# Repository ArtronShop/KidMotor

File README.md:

# KidMotor

บอร์ดขับมอเตอร์สำหรับใช้งานกับ KidBright32 - https://www.ioxhop.com/

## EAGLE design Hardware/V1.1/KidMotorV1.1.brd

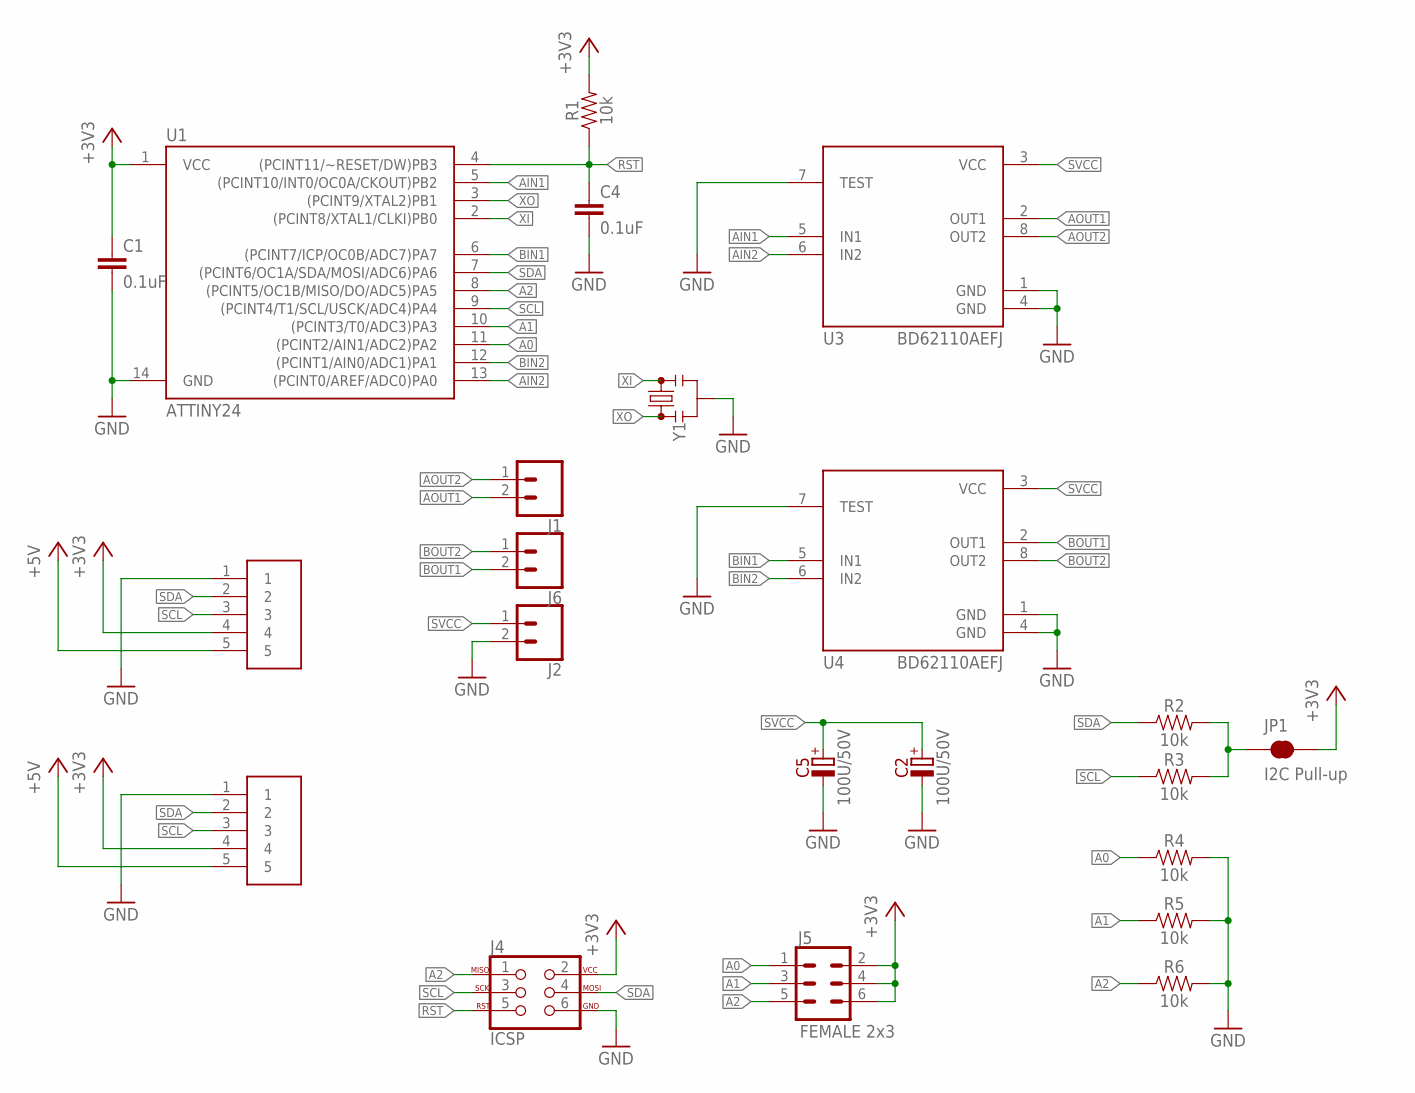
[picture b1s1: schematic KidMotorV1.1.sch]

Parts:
C1, C4: 0.1uF; 0603
C2, C5: 100U/50V; E3,5-8
J1, J2, J6: CONN_025MM; SCREWTERMINAL-5MM-2
J4: ICSP; 2X3
J5: FEMALE 2x3; 2X3
JP1: I2C Pull-up; SMT-JUMPER_2_NC_TRACE_SILK
R1, R2, R3, R4, R5, R6: 10k; 0603
U1: ATTINY24; SO14
U3, U4: BD62110AEFJ; HTSOP-J8
U$2, U$5: JST5PIN
Y1: RESONATORSMD-3.2X1.3; RESONATOR-SMD-3.2X1.3

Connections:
+3V3: C1.1, J4.2, J5.2, J5.4, J5.6, JP1.2, R1.2, U1.1 (VCC), U$2.4, U$5.4
+5V: U$2.5, U$5.5
A0: J5.1, R4.1, U1.11 ((PCINT2/AIN1/ADC2)PA2)
A1: J5.3, R5.1, U1.10 ((PCINT3/T0/ADC3)PA3)
A2: J4.1, J5.5, R6.1, U1.8 ((PCINT5/OC1B/MISO/DO/ADC5)PA5)
AIN1: U1.5 ((PCINT10/INT0/OC0A/CKOUT)PB2), U3.5 (IN1)
AIN2: U1.13 ((PCINT0/AREF/ADC0)PA0), U3.6 (IN2)
AOUT1: J1.2, U3.2 (OUT1)
AOUT2: J1.1, U3.8 (OUT2)
BIN1: U1.6 ((PCINT7/ICP/OC0B/ADC7)PA7), U4.5 (IN1)
BIN2: U1.12 ((PCINT1/AIN0/ADC1)PA1), U4.6 (IN2)
BOUT1: J6.2, U4.2 (OUT1)
BOUT2: J6.1, U4.8 (OUT2)
GND: C1.2, C2.-, C4.2, C5.-, J2.2, J4.6, R4.2, R5.2, R6.2, U1.14 (GND), U3.1 (GND), U3.4 (GND), U3.7 (TEST), U4.1 (GND), U4.4 (GND), U4.7 (TEST), U$2.1, U$5.1, Y1.2
unnamed: JP1.1, R2.2, R3.2
RST: C4.1, J4.5, R1.1, U1.4 ((PCINT11/~RESET/DW)PB3)
SCL: J4.3, R3.1, U1.9 ((PCINT4/T1/SCL/USCK/ADC4)PA4), U$2.3, U$5.3
SDA: J4.4, R2.1, U1.7 ((PCINT6/OC1A/SDA/MOSI/ADC6)PA6), U$2.2, U$5.2
SVCC: C2.+, C5.+, J2.1, U3.3 (VCC), U4.3 (VCC)
XI: U1.2 ((PCINT8/XTAL1/CLKI)PB0), Y1.3
XO: U1.3 ((PCINT9/XTAL2)PB1), Y1.1

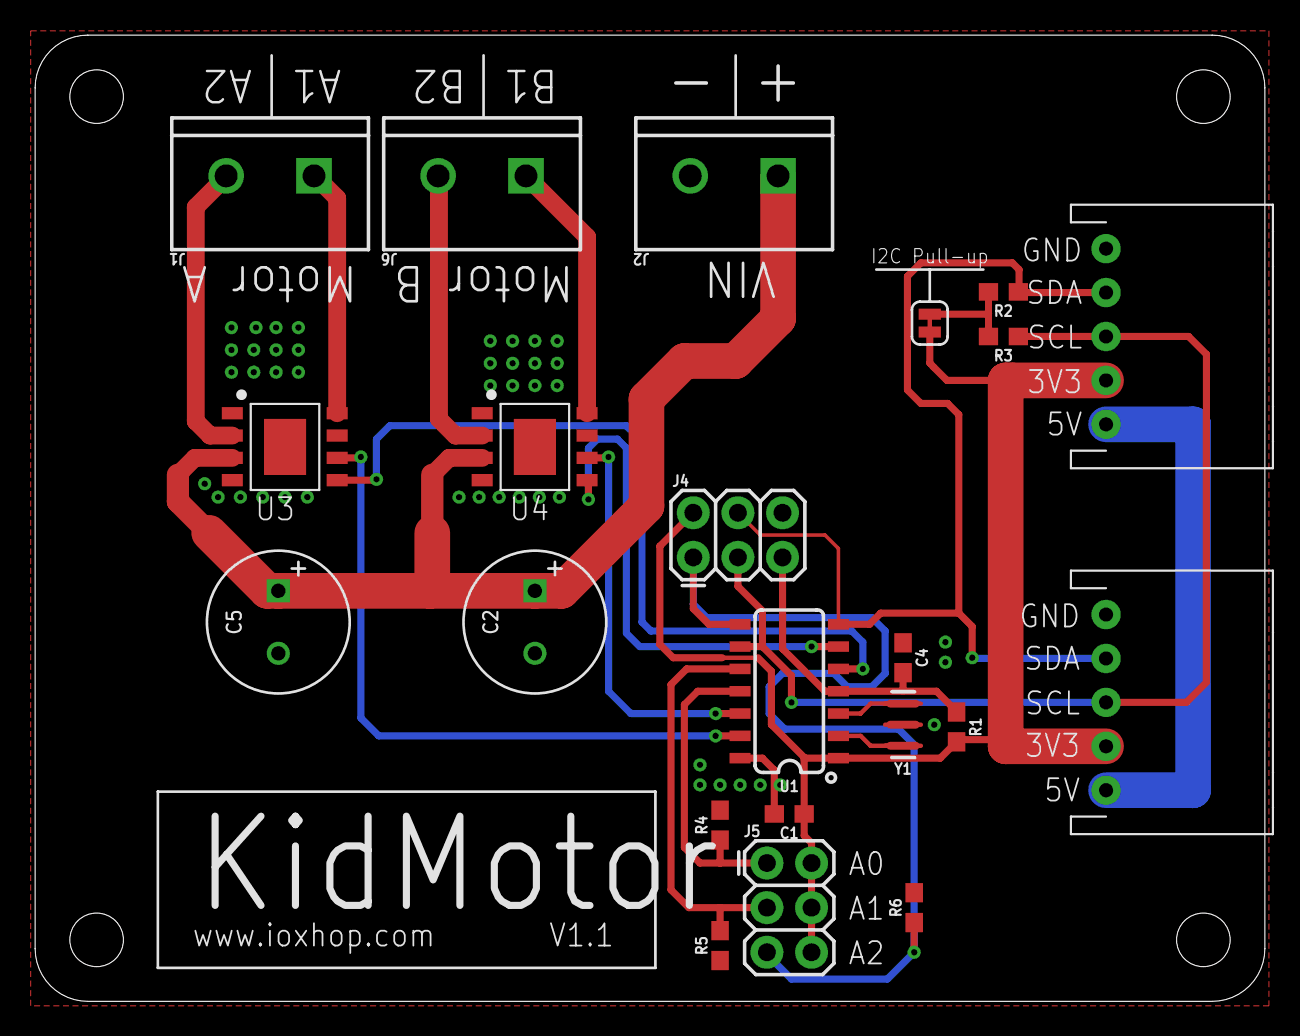
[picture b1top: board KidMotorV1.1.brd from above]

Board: 2 copper layers, 70.0 x 55.0 mm, 22 parts (0 on the bottom side), 21 nets.

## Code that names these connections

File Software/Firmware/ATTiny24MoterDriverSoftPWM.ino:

#include <Arduino.h>
extern "C" {
#include <inttypes.h>
#include <avr/interrupt.h>
#include "USI_TWI_Slave.h"
}

#define DEV_ADDR_OFFSET 0x62
struct PWMTimer {
  uint8_t count;
  uint8_t value;
};

struct {
  PWMTimer CH0_1; // AIN1 -> PB2
  PWMTimer CH0_2; // AIN2 -> PA0
  PWMTimer CH1_1;
  PWMTimer CH1_2;
} SoftPWM;

void setMotor(uint8_t ch, uint8_t dir, uint8_t speed) {
  if (ch == 0) {
    if (dir == 0) { // CH0 -> STOP
      SoftPWM.CH0_1.value = 0;
      SoftPWM.CH0_2.value = 0;
    } else if (dir == 1) { // CH0 -> FORWARD
      SoftPWM.CH0_1.value = 255; // Fix to HIGH
      SoftPWM.CH0_2.value = 255 - speed;
    } else if (dir == 2) { // CH0 -> REVERSE
      SoftPWM.CH0_1.value = 255 - speed;
      SoftPWM.CH0_2.value = 255; // Fix to HIGH
    } else if (dir == 3) { // CH0 -> BRAKE
      SoftPWM.CH0_1.value = 255;
      SoftPWM.CH0_2.value = 255;
    }
  } else if (ch == 1) {
    if (dir == 0) { // CH0 -> STOP
      SoftPWM.CH1_1.value = 0;
      SoftPWM.CH1_2.value = 0;
    } else if (dir == 1) { // CH0 -> FORWARD
      SoftPWM.CH1_1.value = 255; // Fix to HIGH
      SoftPWM.CH1_2.value = 255 - speed;
    } else if (dir == 2) { // CH0 -> REVERSE
      SoftPWM.CH1_1.value = 255 - speed;
      SoftPWM.CH1_2.value = 255; // Fix to HIGH
    } else if (dir == 3) { // CH0 -> BRAKE
      SoftPWM.CH1_1.value = 255;
      SoftPWM.CH1_2.value = 255;
    }
  }
}

/*

  Data: [0] -> Byte 5 - 4 : Dir (0 = STOP, 0b10 = FORWARD, 0b01 = REVERSE, 0b11 = BRAKE)
            -> Byte 0 : Channel (0, 1)
        [1] PWM (0-255)

*/

void onReceiver(uint8_t len) {
  uint8_t buff[len];
  int i;
  for (i = 0; i < len; i++) {
    buff[i] = usiTwiReceiveByte();
  }
  /*
    if (len < 2) {
    return;
    }
  */

  uint8_t Dir = (buff[0] & 0x30) >> 4;
  uint8_t Channel = buff[0] & 0x01;
  uint8_t PWM = buff[1];
  setMotor(Channel, Dir, PWM);
}

void onRequest() {
  usiTwiTransmitByte(0x00);
}

void setup() {
  // Setup I/O
  DDRA = 0x83; // PA0 1 and 7 is OUTPUT, Other is INPUT
  DDRB = 0x04; // PB2 only

  uint8_t address = DEV_ADDR_OFFSET;

  // PORTA2
  if (PINA&(1<<2)) {
    address += 1;
  }

  // PORTA3
  if (PINA&(1<<3)) {
    address += 2;
  }

  // PORTA5
  if (PINA&(1<<5)) {
    address += 4;
  }

  // Setup I2C Slave
  usiTwiSlaveInit(address);

  // Set callback
  usi_onRequestPtr = onRequest;
  usi_onReceiverPtr = onReceiver;

  //setMotor(0, 2, 40);
}

void loop() {
  // AIN1
  if (SoftPWM.CH0_1.value == 255) {
    PORTB |= (1 << 2);
  } else if (SoftPWM.CH0_1.value == 0) {
    PORTB &= ~(1 << 2);
  } else {
    if (SoftPWM.CH0_1.count < SoftPWM.CH0_1.value)
      PORTB |= (1 << 2);
    else
      PORTB &= ~(1 << 2);
    SoftPWM.CH0_1.count++;
  }

  // AIN2
  if (SoftPWM.CH0_2.value == 255) {
    PORTA |= 0x01;
  } else if (SoftPWM.CH0_2.value == 0) {
    PORTA &= ~(0x01);
  } else {
    if (SoftPWM.CH0_2.count < SoftPWM.CH0_2.value)
      PORTA |= 0x01;
    else
      PORTA &= ~(0x01);
    SoftPWM.CH0_2.count++;
  }

  // BIN1
  if (SoftPWM.CH1_1.value == 255) {
    PORTA |= (1 << 7);
  } else if (SoftPWM.CH1_1.value == 0) {
    PORTA &= ~(1 << 7);
  } else {
    if (SoftPWM.CH1_1.count < SoftPWM.CH1_1.value)
      PORTA |= (1 << 7);
    else
      PORTA &= ~(1 << 7);
    SoftPWM.CH1_1.count++;
  }

  // BIN2
  if (SoftPWM.CH1_2.value == 255) {
    PORTA |= (1 << 1);
  } else if (SoftPWM.CH1_2.value == 0) {
    PORTA &= ~(1 << 1);
  } else {
    if (SoftPWM.CH1_2.count < SoftPWM.CH1_2.value)
      PORTA |= (1 << 1);
    else
      PORTA &= ~(1 << 1);
    SoftPWM.CH1_2.count++;
  }

  // Wire Stop Check
  if (!usi_onReceiverPtr) return;                         // no onReceive callback, nothing to do...
  if (!(USISR & (1 << USIPF))) return;                    // Stop not detected
  uint8_t amount = usiTwiAmountDataInReceiveBuffer();
  if (amount == 0) return;                                // no data in buffer
  usi_onReceiverPtr(amount);
}

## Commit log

2018-12-02 V1.1
2018-12-02 แก้ชื่อโฟลเดอร์

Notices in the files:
parts and their libraries:
SparkFun-Capacitors: Licensing: Creative Commons ShareAlike 4.0 International - https://creativecommons.org/licenses/by-sa/4.0
